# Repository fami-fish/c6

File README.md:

# c6
A split keyboard utilizing an xiao rp2040 or nrf microcontroller.

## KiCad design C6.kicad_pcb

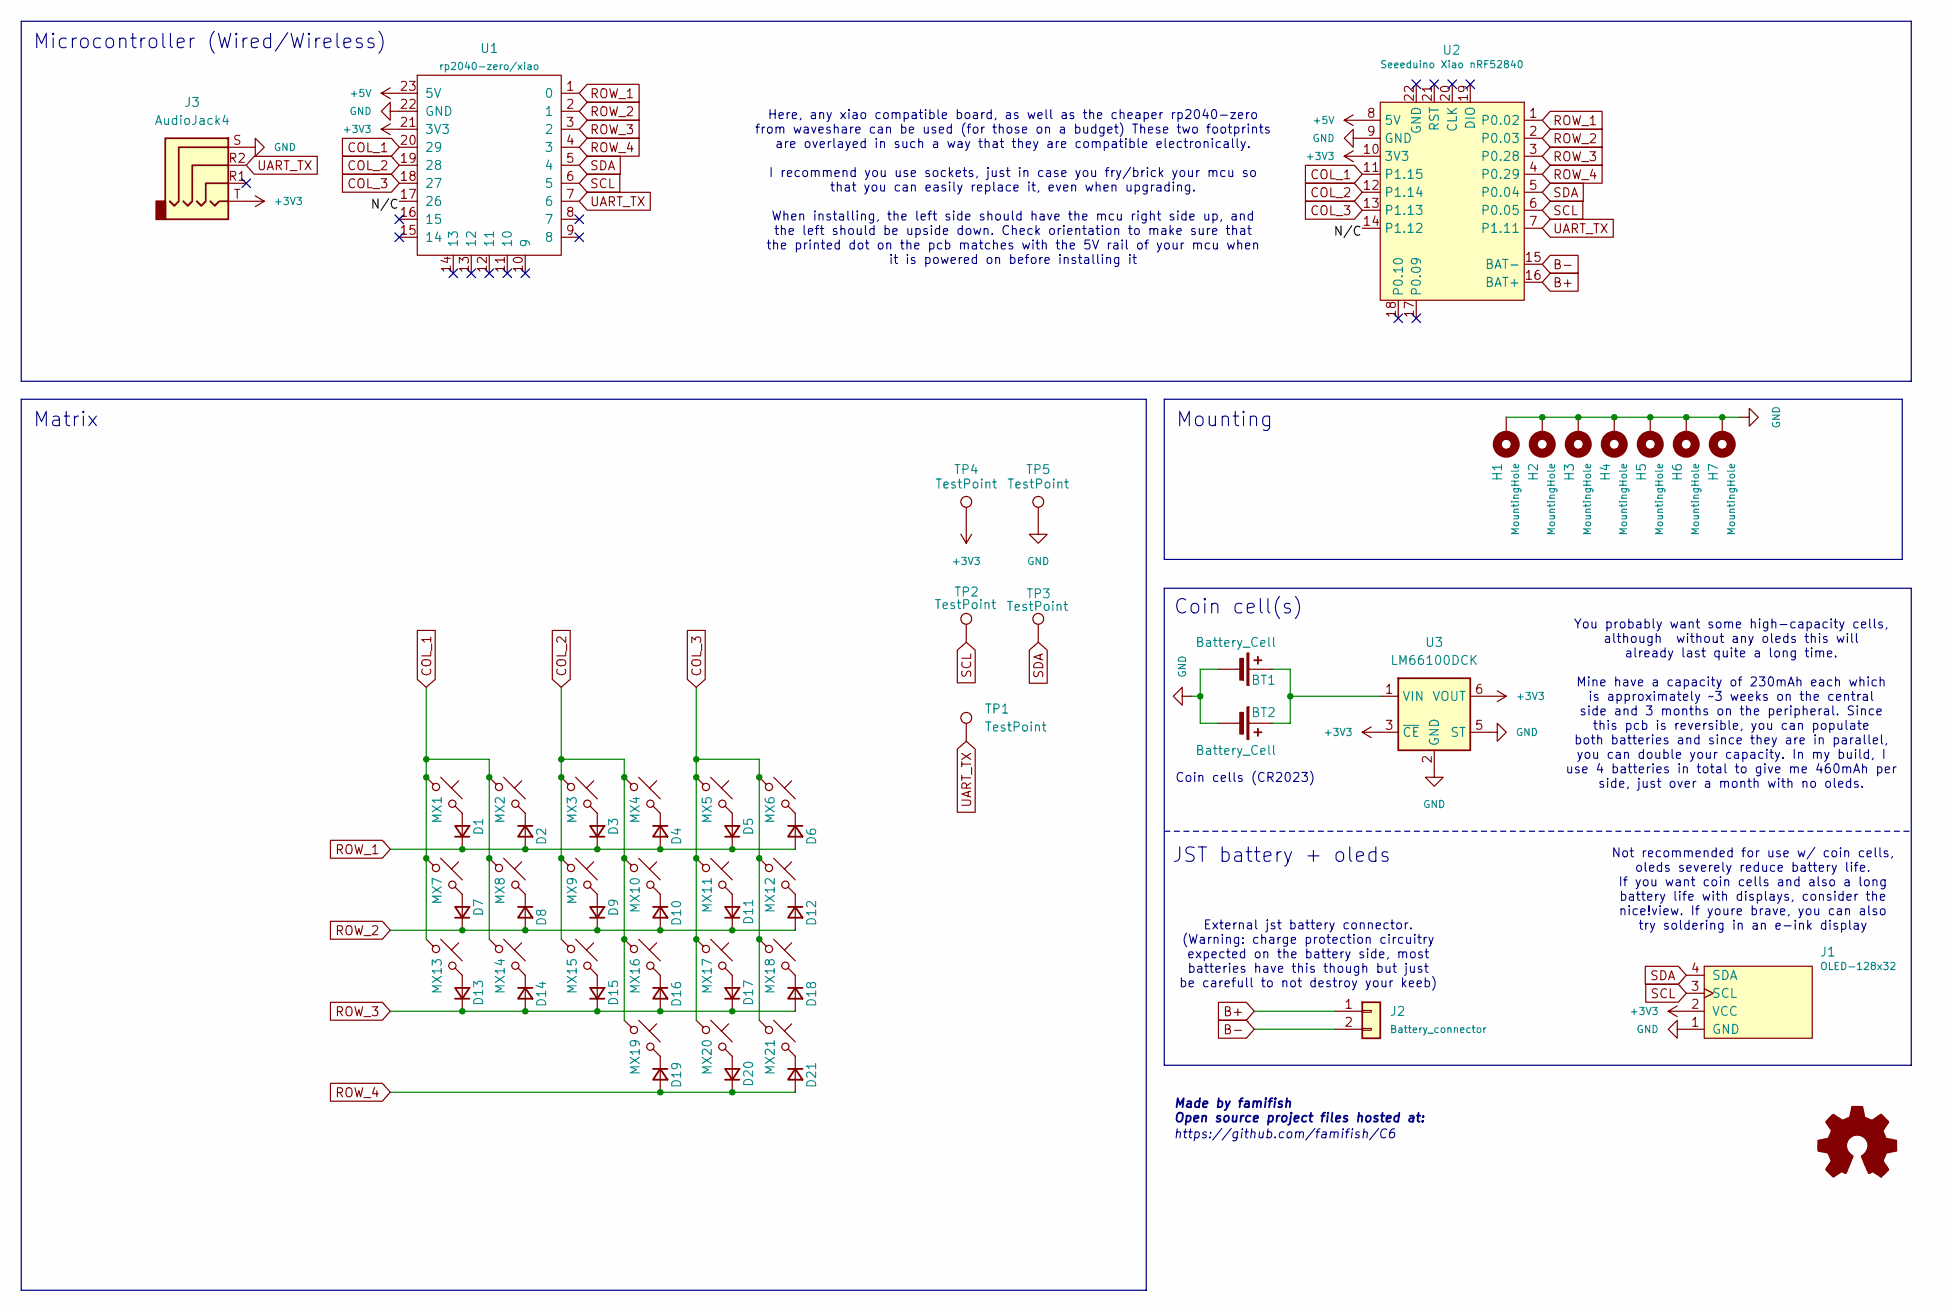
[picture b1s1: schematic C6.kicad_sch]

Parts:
BT1, BT2: Battery_Cell; BatteryHolder_Keystone_3034_1x20mm_HandSolder_design
D1, D2, D3, D4, D5, D6, D7, D8, D9, D10, D11, D12, D13, D14, D15, D16, D17, D18, D19, D20, D21: D_Small; Diode_THT_SMD
H1, H2, H3, H4, H5, H6, H7: MountingHole; MountingHole_2.2mm_M2_Pad
J1: OLED-128x32; OLED-128x32-double-sided
J2: Battery_connector; JST_PH_S2B-PH-K_1x02_P2.00mm_Horizontal_Reversible
J3: AudioJack4; CON_MJ-4PP-9_Reversible
MX1, MX2, MX3, MX4, MX5, MX6, MX7, MX8, MX9, MX10, MX11, MX12, MX13, MX14, MX15, MX16, MX17, MX18, MX20: MX_SW_solder; MX-Optional-Reversible-1U
MX19, MX21: MX_SW_solder; MX-Optional-Reversible-1.5U
TP1, TP2, TP3, TP4, TP5: TestPoint; TestPoint_Pad_D1.5mm
U1: rp2040-zero/xiao; rp2040-zero-tht
U2: Seeeduino Xiao nRF52840; Xiao_nRF52840_AH_Pogo
U3: LM66100DCK; SOT-363_SC-70-6_Handsoldering

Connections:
+3V3: J1.2 (VCC), J3.T, TP4.1, U1.21 (3V3), U2.10 (3V3), U3.3 (~CE), U3.6 (VOUT)
+5V: U1.23 (5V), U2.8 (5V)
/N/C: U1.17 (26), U2.14 (P1.12)
B+: J2.1, U2.16 (BAT+)
B-: J2.2, U2.15 (BAT-)
COL_1: MX1.1, MX2.1, MX7.1, MX8.1, MX13.1, MX14.1, U1.20 (29), U2.11 (P1.15)
COL_2: MX3.1, MX4.1, MX9.1, MX10.1, MX15.1, MX16.1, MX19.1, U1.19 (28), U2.12 (P1.14)
COL_3: MX5.1, MX6.1, MX11.1, MX12.1, MX17.1, MX18.1, MX20.1, MX21.1, U1.18 (27), U2.13 (P1.13)
GND: BT1.2 (-), BT2.2 (-), H1.1, H2.1, H3.1, H4.1, H5.1, H6.1, H7.1, J1.1 (GND), J3.S, TP5.1, U1.22 (GND), U2.9 (GND), U3.2 (GND), U3.5 (ST); also elsewhere on the board
unnamed 9: BT1.1 (+), BT2.1 (+), U3.1 (VIN); also elsewhere on the board
unnamed: D1.2 (A), MX1.2
unnamed: D2.1 (K), MX2.2
unnamed: D3.2 (A), MX3.2
unnamed: D4.1 (K), MX4.2
unnamed: D5.2 (A), MX5.2
unnamed: D6.1 (K), MX6.2
unnamed: D7.2 (A), MX7.2
unnamed: D8.1 (K), MX8.2
unnamed: D9.2 (A), MX9.2
unnamed: D10.1 (K), MX10.2
unnamed: D11.2 (A), MX11.2
unnamed: D12.1 (K), MX12.2
unnamed: D13.2 (A), MX13.2
unnamed: D14.1 (K), MX14.2
unnamed: D15.2 (A), MX15.2
unnamed: D16.1 (K), MX16.2
unnamed: D17.2 (A), MX17.2
unnamed: D18.1 (K), MX18.2
unnamed: D19.1 (K), MX19.2
unnamed: D20.2 (A), MX20.2
unnamed: D21.1 (K), MX21.2
ROW_1: D1.1 (K), D2.2 (A), D3.1 (K), D4.2 (A), D5.1 (K), D6.2 (A), U1.1 (0), U2.1 (P0.02)
ROW_2: D7.1 (K), D8.2 (A), D9.1 (K), D10.2 (A), D11.1 (K), D12.2 (A), U1.2 (1), U2.2 (P0.03)
ROW_3: D13.1 (K), D14.2 (A), D15.1 (K), D16.2 (A), D17.1 (K), D18.2 (A), U1.3 (2), U2.3 (P0.28)
ROW_4: D19.2 (A), D20.1 (K), D21.2 (A), U1.4 (3), U2.4 (P0.29)
SCL: J1.3 (SCL), TP2.1, U1.6 (5), U2.6 (P0.05)
SDA: J1.4 (SDA), TP3.1, U1.5 (4), U2.5 (P0.04)
UART_TX: J3.R2, TP1.1, U1.7 (6), U2.7 (P1.11)

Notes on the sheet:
Mounting
Microcontroller (Wired/Wireless)
Matrix
JST battery + oleds
External jst battery connector. (Warning: charge protection circuitry expected on the battery side, most batteries have this though but just be carefull to not destroy your keeb)
You probably want some high-capacity cells, although without any oleds this will already last quite a long time. Mine have a capacity of 230mAh each which is approximately ~3 weeks on the central side and 3 months on the peripheral. Since this pcb is reversible, you can populate both batteries and 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
Made by famifish Open source project files hosted at:
Coin cell(s)
Not recommended for use w/ coin cells, oleds severely reduce battery life. If you want coin cells and also a long battery life with displays, consider the nice!view. If youre brave, you can also try soldering in an e-ink display
https://github.com/famifish/C6
Here, any xiao compatible board, as well as the cheaper rp2040-zero from waveshare can be used (for those on a budget) These two footprints are overlayed in such a way that they are compatible electronically. I recommend you use sockets, just in case you fry/brick your mcu so that you can easily re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
Coin cells (CR2023)

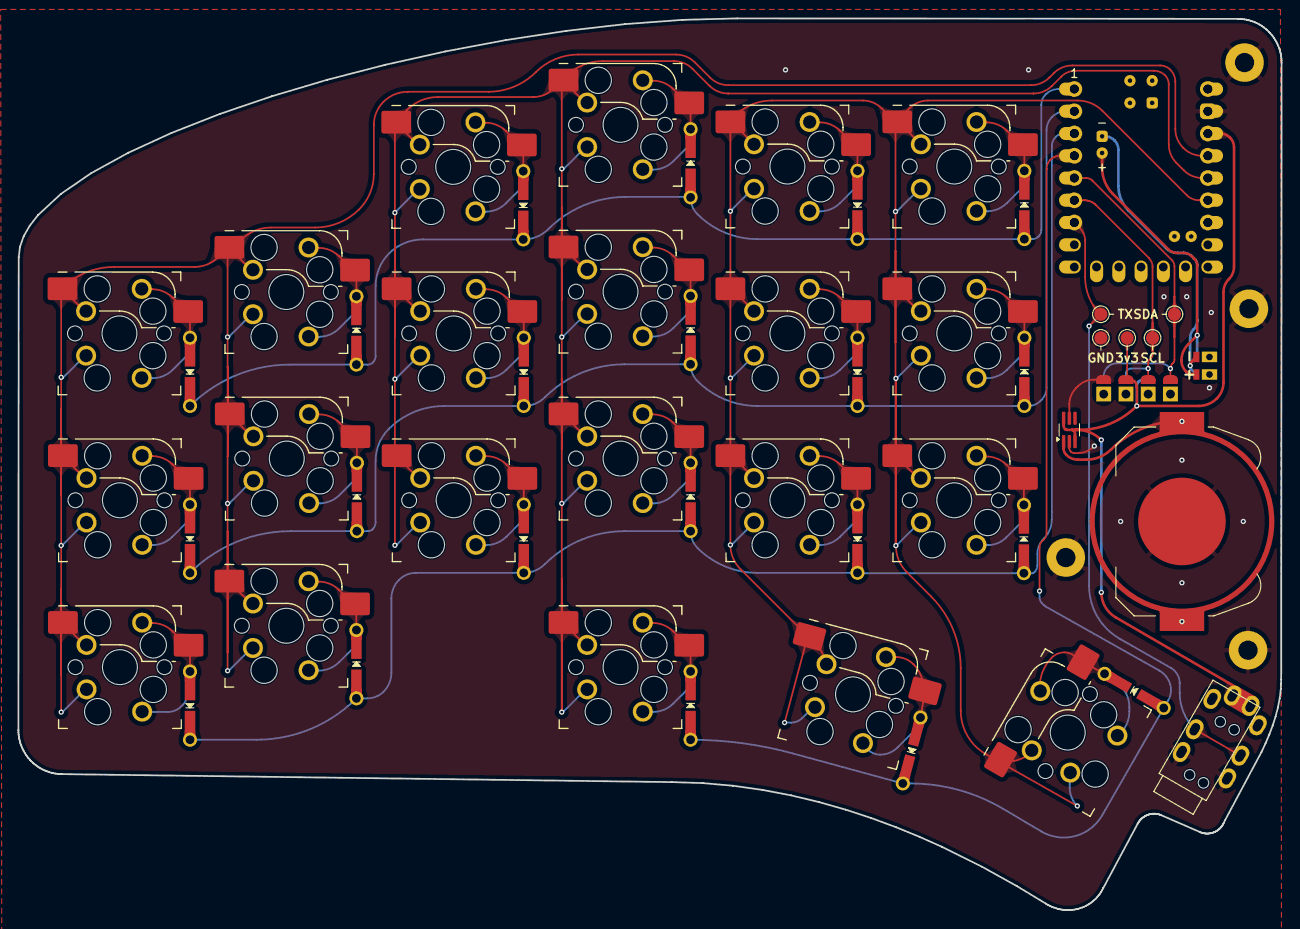
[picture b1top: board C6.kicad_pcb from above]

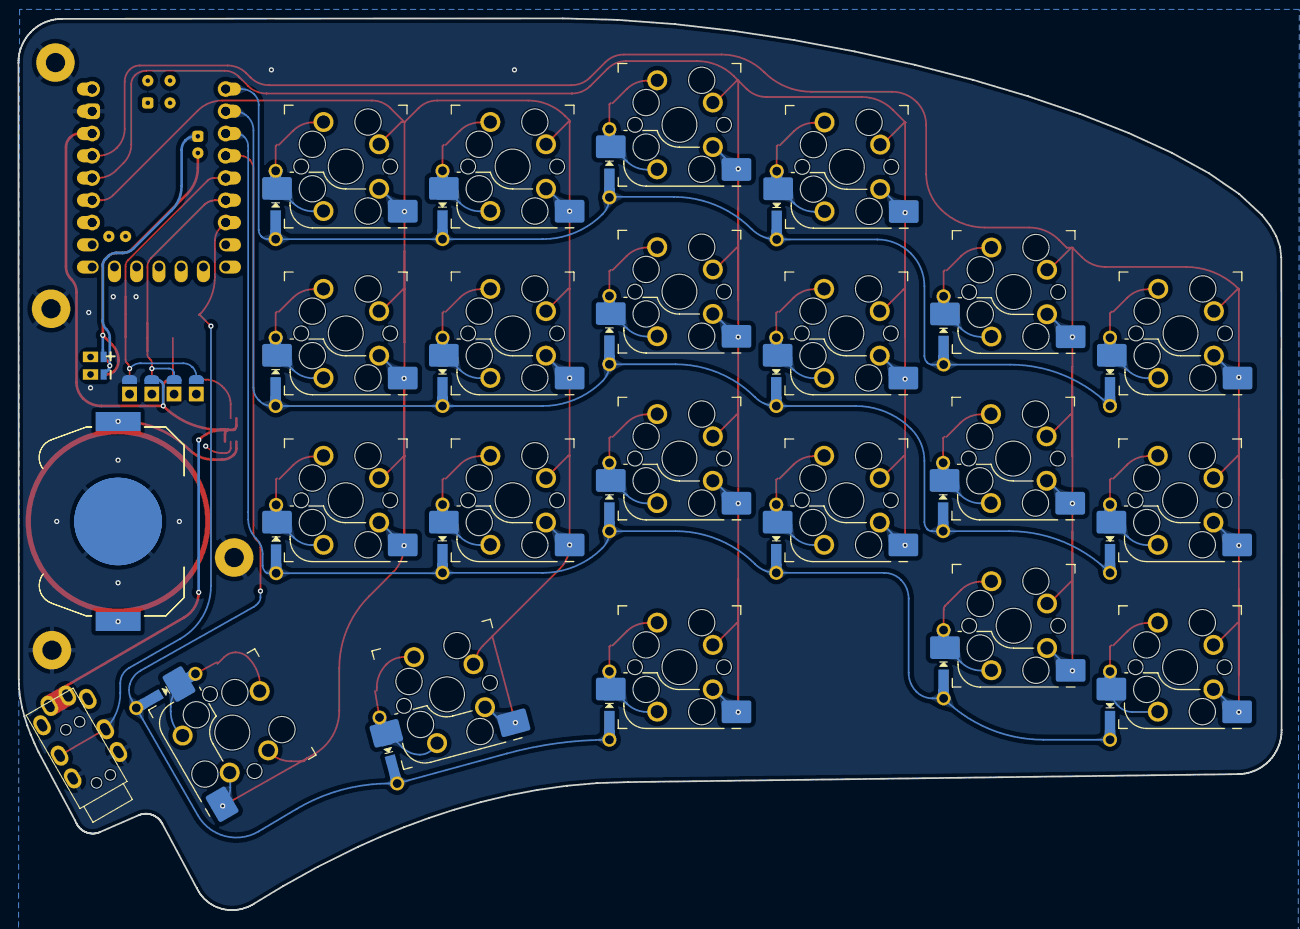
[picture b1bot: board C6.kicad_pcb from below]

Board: 2 copper layers, 144.2 x 101.8 mm, 60 parts (5 on the bottom side), 38 nets.

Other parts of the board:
BT1#2: Battery_Cell; BatteryHolder_Keystone_3034_1x20mm_HandSolder_design

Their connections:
GND: BT1#2.2 (-); also elsewhere on the board
unnamed 9: BT1#2.1 (+); also elsewhere on the board

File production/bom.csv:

Designator,Footprint,Quantity,Value,LCSC Part #
"BT1_2, BT1, BT2",BatteryHolder_Keystone_3034_1x20mm_HandSolder_design,3,Battery_Cell,
"D1, D10, D11, D12, D13, D14, D15, D16, D17, D18, D19, D2, D20, D21, D3, D4, D5, D6, D7, D8, D9",Diode_THT_SMD,21,D_Small,
J1,OLED-128x32-double-sided,1,OLED-128x32,
J2,JST_PH_S2B-PH-K_1x02_P2.00mm_Horizontal_Reversible,1,Battery_connector,
J3,CON_MJ-4PP-9_Reversible,1,AudioJack4,
"MX1, MX10, MX11, MX12, MX13, MX14, MX15, MX16, MX17, MX18, MX2, MX20, MX3, MX4, MX5, MX6, MX7, MX8, MX9",MX-Optional-Reversible-1U,19,MX_SW_solder,
"MX19, MX21",MX-Optional-Reversible-1.5U,2,MX_SW_solder,
"TP1, TP2, TP3, TP4, TP5",TestPoint_Pad_D1.5mm,5,TestPoint,
U1,rp2040-zero-tht,1,rp2040-zero/xiao,
U3,SOT-363_SC-70-6_Handsoldering,1,LM66100DCK,

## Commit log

2024-07-24 Schematic
2024-11-28 creation of PCB files
